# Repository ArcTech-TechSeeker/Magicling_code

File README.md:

# Magicling_code（nIpxel用コード）

モーション入力＆ハプティクス付き **無線コントローラ nIpxel**（ESP32 + BNO055）を中心としたコード/回路/CADである。
9 軸センサから得た姿勢・加速度を**世界座標へ変換**し、**Bluetooth SPP** でホストへ送出すると同時に、振動モータを **PWM** で制御する。

紹介サイト：https://nipxel.netlify.app/

---

## 特長

* **9軸姿勢融合**：BNO055（NDOF）から **Yaw / Pitch / Roll** と **線形加速度**を取得
* **座標安定化**：クォータニオン→回転行列で**グローバル座標系加速度**を算出
* **ジャンプ補償**：Yaw のスパイク（磁気外乱等）を短時間固定＋オフセットで自然連続化
* **ハプティクス**：振動モータを **200 Hz / 8bit PWM** で駆動（アナログ追従／点滅パターン）
* **軽量通信**：Bluetooth SPP で **固定小数バイナリ**（15 B/フレーム）を周期送信
* **2P対応**：デバイス名末尾を `"1P"` / `"2P"` で切替

---

## アーキテクチャ

```
BNO055 → (I²C) → ESP32 (LoLin32 Lite 等)
         ├─ クォータニオン姿勢 → 回転行列 → 世界座標加速度
         ├─ ジャンプ補償（Yaw offset）
         ├─ ハプティクス制御（PWM）
         └─ Bluetooth SPP（固定小数バイナリ）→ PC / ゲーム
```

---

## ハードウェア

* **MCU**：ESP32（LoLin32 Lite 等）
* **IMU**：Adafruit BNO055（I²C, アドレス `0x29`）
* **モータ**：小型振動モータ（ローサイド NPN 駆動：2SC1815）
* **ベース抵抗**：**1 kΩ（茶・黒・赤・金）**
* **フライバック**：1N400x 等（モータ端子**並列・逆向き**）

### 回路データ
回路データはCircuitフォルダ内のもの．Kicadを用いて作成されている．

PCBを発注したければ，GaberのZIPファイルを直接JLCPCBなどのサービスに発注するとよい

### CADデータ
AutodeskのInventorを用いて製作．プリントしたい場合はfor 3Dprintフォルダ内のSTLを使用

### 既定ピン

| 機能       | ESP32 ピン    | 備考                  |
| -------- | ----------- | ------------------- |
| I²C SDA  | GPIO **23** | `Wire.begin(23,19)` |
| I²C SCL  | GPIO **19** | 〃                   |
| PWM（モータ） | GPIO **25** | 200 Hz / 8bit       |
| LED      | GPIO **22** | 動作表示                |

> 3.3 V／GND 共有。I²C は 4.7–10 kΩ のプルアップ（多くのブレークアウトに実装済み）。

---

## ファームウェア概要

### 主要ライブラリ

`Wire.h`（I²C）、`Adafruit_BNO055.h`（9軸融合）、`utility/imumaths.h`（Quat/行列）、`BluetoothSerial.h`（SPP）

### PWM 互換層

ESP32 Arduino Core v2/v3 の差異をマクロで吸収（`ledcSetup/AttachPin` vs `ledcAttach`）。

### センサ処理パイプライン

1. **取得**：BNO055 から **線形加速度**・**オイラー角**・**クォータニオン**
2. **平滑化**：加速度[g]に一次 IIR（`alpha=0.7`）
3. **座標変換**：Quat→3×3 回転行列でローカル→**世界座標系**へ
4. **Yaw 補償**：差分 > 45°（かつ < 320°）を「ジャンプ」とみなし短時間固定、後段で `yaw_offset` を適用

### ハプティクス（`Vibration()`）

* **モード選択**：SPP で `'0'..'5'` の一文字コマンド

  * `'0'`：アナログ追従（|a| からデューティ算出、下限デッドゾーン・上限クランプ）
  * `'1'..'4'`：点滅パターン（周期×デューティ）
  * `'5'`：停止

---

## Bluetooth SPP プロトコル

**1 フレーム = 15 バイト**

* 先頭ヘッダ：`'S'`（1 B）
* ペイロード：**int16 × 7**（14 B, Little-Endian）

  1. `ax_global × 100`（2桁固定小数）
  2. `ay_global × 100`
  3. `az_global × 100`
  4. `qw × 10000`（4桁固定小数）
  5. `qx × 10000`
  6. `qy × 10000`
  7. `qz × 10000`

**送信周期**：およそ **100 Hz**（`delay(10)` 目安）
**デコード（受信側）**：LE の `int16` を実数に復元（加速度÷100、Quaternion÷10000）。ヘッダ `'S'` で同期。

---

## ビルド & 書き込み

### Arduino IDE

1. ボード：ESP32 ファミリ（LoLin32 Lite 等）
2. 依存ライブラリ導入（Adafruit BNO055 ほか）
3. スケッチを書き込み

### PlatformIO / ESP-IDF

* `ledc` / `Wire` / `BluetoothSerial` が利用可能な環境設定でビルド。

---

## 起動と使用

1. 電源投入／SPP ペアリング：デバイス名は `"LOLIN32_Lite_1P"`（`name` で `"2P"` に切替可）
2. ホストは SPP で **15B 固定フレーム**を連続受信
3. 必要に応じ `'0'..'5'` を送信して**ハプティクスモード**を切替

---

## 調整可能パラメータ

| 変数              |     既定 | 説明         |
| --------------- | -----: | ---------- |
| `alpha`         |    0.7 | ローパス（過去重み） |
| `pwmFreq`       | 200 Hz | モータ駆動周波数   |
| `pwmResolution` |  8 bit | デューティ分解能   |
| `j_wall`        |  2 ループ | Yaw 固定期間   |
| `name`          | `"1P"` | SPP 名末尾    |

---

## リポジトリ構成（例）

```
Magicling_code/
├── src/                # ESP32 スケッチ/ソース
├── include/            # ヘッダ
├── hardware/           # 回路図・配線図
└── README.md
```

> 実際の構成はリポジトリに従うこと。名称や配置は変更される場合がある。

## ライセンス

リポジトリ同梱の **LICENSE** を参照。
# Magicling_code (Code for nIpxel)

This repository contains the code, circuit data, and CAD resources centered around **nIpxel**, a **wireless controller with motion input and haptics** (ESP32 + BNO055).

It converts orientation/acceleration obtained from a 9-axis sensor into the **world (global) coordinate frame**, transmits the data to a host via **Bluetooth SPP**, and controls a vibration motor using **PWM**.

Project site: https://nipxel.netlify.app/

---

## Features

- **9-axis sensor fusion**: Uses BNO055 (NDOF) to obtain **Yaw / Pitch / Roll** and **linear acceleration**
- **Coordinate stabilization**: Converts quaternion → rotation matrix to compute **global-frame acceleration**
- **Jump compensation**: Detects yaw spikes (e.g., magnetic disturbance), briefly freezes + applies an offset for smooth continuity
- **Haptics**: Drives a vibration motor at **200 Hz / 8-bit PWM** (analog follow / blink patterns)
- **Lightweight transport**: Periodically sends **fixed-point binary** frames over Bluetooth SPP (**15 B/frame**)
- **Two-player support**: Switch the device name suffix to `"1P"` / `"2P"`

---

## Architecture

```text
BNO055 → (I²C) → ESP32 (LoLin32 Lite, etc.)
         ├─ Quaternion orientation → Rotation matrix → World-frame acceleration
         ├─ Jump compensation (yaw offset)
         ├─ Haptics control (PWM)
         └─ Bluetooth SPP (fixed-point binary) → PC / game
```

---

## Hardware

- **MCU**: ESP32 (LoLin32 Lite, etc.)
- **IMU**: Adafruit BNO055 (I²C, address `0x29`)
- **Motor**: Small vibration motor (low-side NPN drive: 2SC1815)
- **Base resistor**: **1 kΩ (brown-black-red-gold)**
- **Flyback diode**: 1N400x, etc. (in parallel across motor terminals, reverse polarity)

### Circuit Data

Circuit data is located in the `Circuit` folder and was created using **KiCad**.

If you want to order a PCB, you can upload the **Gerber ZIP** directly to services such as **JLCPCB**.

### CAD Data

Designed using **Autodesk Inventor**. For 3D printing, use the STL files in the `for 3Dprint` folder.

### Default Pins

| Function        | ESP32 Pin     | Notes               |
|----------------|---------------|---------------------|
| I²C SDA        | GPIO **23**   | `Wire.begin(23,19)` |
| I²C SCL        | GPIO **19**   | same as above       |
| PWM (motor)    | GPIO **25**   | 200 Hz / 8-bit      |
| LED            | GPIO **22**   | status indicator    |

> Share 3.3 V / GND. I²C requires 4.7–10 kΩ pull-ups (often included on breakout boards).

---

## Firmware Overview

### Key Libraries

`Wire.h` (I²C), `Adafruit_BNO055.h` (sensor fusion), `utility/imumaths.h` (Quat/matrix), `BluetoothSerial.h` (SPP)

### PWM Compatibility Layer

Absorbs differences between ESP32 Arduino Core v2/v3 using macros (e.g., `ledcSetup/AttachPin` vs `ledcAttach`).

### Sensor Processing Pipeline

1. **Read**: From BNO055: **linear acceleration**, **Euler angles**, **quaternion**
2. **Smoothing**: First-order IIR on acceleration [g] (`alpha=0.7`)
3. **Transform**: Quat → 3×3 rotation matrix; local → **world frame**
4. **Yaw compensation**: If delta > 45° (and < 320°), treat as a “jump”, freeze briefly; apply `yaw_offset` afterward

### Haptics (`Vibration()`)

- **Mode selection**: Send a single-character command via SPP: `'0'..'5'`

  - `'0'`: Analog follow (compute duty from |a| with deadzone and clamp)
  - `'1'..'4'`: Blink patterns (period × duty)
  - `'5'`: Stop

---

## Bluetooth SPP Protocol

**1 frame = 15 bytes**

- Header: `'S'` (1 B)
- Payload: **int16 × 7** (14 B, Little-Endian)

  1. `ax_global × 100` (fixed-point with 2 decimals)
  2. `ay_global × 100`
  3. `az_global × 100`
  4. `qw × 10000` (fixed-point with 4 decimals)
  5. `qx × 10000`
  6. `qy × 10000`
  7. `qz × 10000`

**Transmit rate**: approx. **100 Hz** (target via `delay(10)`)  
**Decode (receiver)**: Convert LE `int16` back to float (accel ÷ 100, quaternion ÷ 10000). Use header `'S'` for synchronization.

---

## Build & Flash

### Arduino IDE

1. Board: ESP32 family (LoLin32 Lite, etc.)
2. Install dependencies (Adafruit BNO055, etc.)
3. Upload the sketch

### PlatformIO / ESP-IDF

- Build with an environment where `ledc`, `Wire`, and `BluetoothSerial` are available.

---

## Startup & Usage

1. Power on / pair via SPP: device name defaults to `"LOLIN32_Lite_1P"` (set `name` to switch to `"2P"`)
2. Host continuously receives **15-byte fixed frames** over SPP
3. Send `'0'..'5'` as needed to switch **haptics modes**

---

## Tunable Parameters

| Variable          | Default  | Description            |
|------------------|---------:|------------------------|
| `alpha`          |    0.7   | Low-pass filter weight |
| `pwmFreq`        | 200 Hz   | Motor drive frequency  |
| `pwmResolution`  |  8 bit   | PWM duty resolution    |
| `j_wall`         | 2 loops  | Yaw freeze duration    |
| `name`           | `"1P"`   | SPP name suffix        |

---

## Repository Layout (Example)

```text
Magicling_code/
├── src/                # ESP32 sketch/source
├── include/            # headers
├── hardware/           # schematics/wiring
└── README.md
```

> Follow the actual repository structure. Names and locations may change.

---

## License

See the **LICENSE** file included in this repository.

---

## BLE OTA

The firmware exposes the same BLE OTA protocol as
`naka6ryo/RemoteCompilerToMicon` WebAppSide, without adding Wi-Fi
provisioning.

* BLE device name during the first 10 seconds after boot:
  `ESP32-nIpxel_1P` or `ESP32-nIpxel_2P`
* OTA service: `9f5f0001-8d9e-6f4e-bd0c-3c4d5e6f7180`
* Control: `START:<size>`, `END`, `ABORT`
* Data: binary firmware chunks
* Status: `READY`, `PROGRESS:x/y`, `SUCCESS`, `ERROR:*`

Use an ESP32 partition scheme with OTA slots. The VS Code/Arduino CLI settings
use `PartitionScheme=min_spiffs`, which gives the OTA app slot 1,966,080 bytes.
The PlatformIO settings use `partitions_ota_2m.csv`, matching the referenced
BLE OTA project.

## Game BLE Service

The device also exposes the game-facing BLE service used by
`BleControllerAdapter.js`.

* BLE device name after the OTA pairing window: `nIpxel_1P` or `nIpxel_2P`
* Service: `12345678-1234-1234-1234-123456789abc`
* Sensor Notify: `12345678-1234-1234-1234-123456789abd`
* Haptic Write: `12345678-1234-1234-1234-123456789abe`
* Sensor frame: 17 bytes, `S` + sequence byte + seven little-endian `int16` values + flags byte
* Haptic command: 2 bytes, `strength` and `duration` in 10 ms units

Arduino CLI build outputs are written to the workspace-local `build/` folder.

BLE advertising is mode-switched to keep Web Bluetooth filters reliable:
the first 10 seconds after boot advertise only the OTA service, and then the
device advertises only the game service. If an OTA client connects during that
initial window, OTA mode is kept active while connected.

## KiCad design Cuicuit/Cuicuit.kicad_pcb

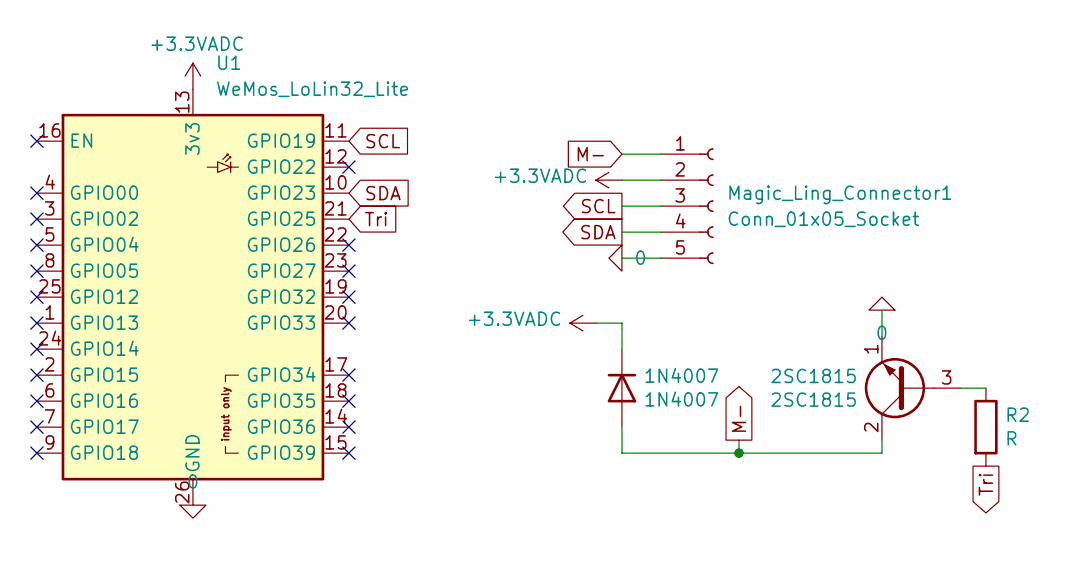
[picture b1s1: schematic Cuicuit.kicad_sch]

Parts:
1N4007: 1N4007; R_Axial_DIN0207_L6.3mm_D2.5mm_P10.16mm_Horizontal
2SC1815: 2SC1815; TO-92_Inline_Wide
Magic_Ling_Connector1: Conn_01x05_Socket; JST_PH_B5B-PH-K_1x05_P2.00mm_Vertical
R2: R; R_Axial_DIN0207_L6.3mm_D2.5mm_P10.16mm_Horizontal
U1: WeMos_LoLin32_Lite; WEMOS_LoLin32_Lite

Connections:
0: 2SC1815.1 (E), Magic_Ling_Connector1.5, U1.26 (GND)
+3.3VADC: 1N4007.1 (K), Magic_Ling_Connector1.2, U1.13 (3v3)
M-: 1N4007.2 (A), 2SC1815.2 (C), Magic_Ling_Connector1.1
unnamed: 2SC1815.3 (B), R2.1
SCL: Magic_Ling_Connector1.3, U1.11 (GPIO19)
SDA: Magic_Ling_Connector1.4, U1.10 (GPIO23)
Tri: R2.2, U1.21 (GPIO25)

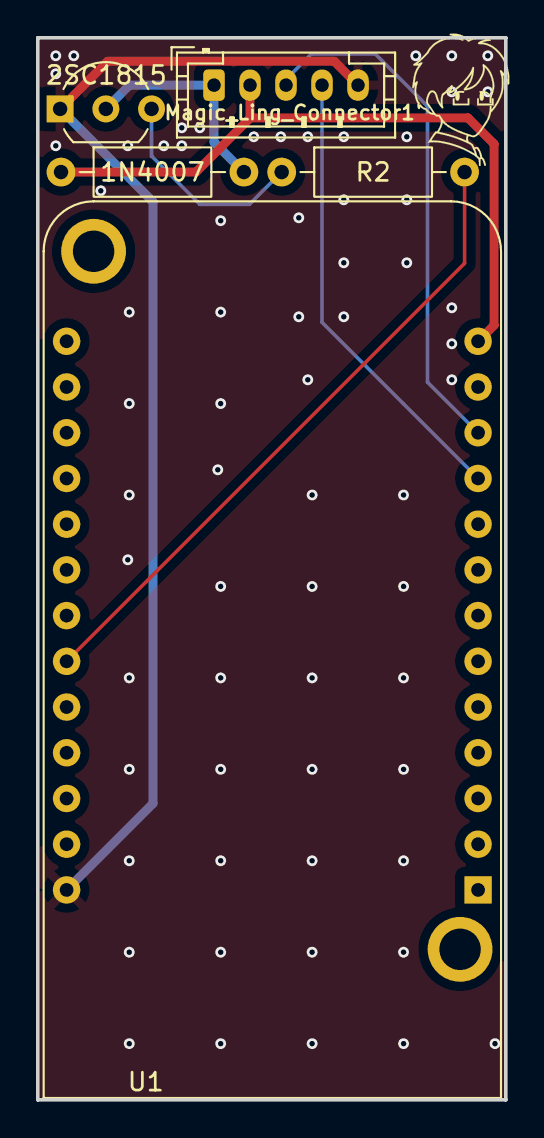
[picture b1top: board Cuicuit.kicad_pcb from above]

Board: 2 copper layers, 26.0 x 59.0 mm, 5 parts (0 on the bottom side), 7 nets.

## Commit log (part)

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2025-07-31 VScode上での書き込みの実装
2025-07-31 攻撃判定時に画面を白く光らす
2025-08-01 attack時の向いている向きの取得の試み（Yawのオイラーの値の飛びを判定して補正する）
2025-08-01 Yaw角の値の飛びの修正
2025-08-01 コードを関数を用いて整理，コメントの追加
2025-08-01 attack_yawの文字の色の変更
2025-08-02 振動モータ機能の追加（加速度により強さが変化）
2025-08-06 Bluetooth通信と詠唱状態（Spell：指を立てる，Spell2：動かし続ける）の追加
2025-08-06 名前変更
2025-08-08 ちょい変
2025-08-21 Lolin用の更新およびライブラシの整理
2025-08-21 ライブラリ対応
2025-08-22 判定の微調整
2025-09-24 加速度と３軸角度の通信
2025-09-27 受信の改良
2025-10-06 方向修正プログラムの実装
2025-10-07 ピッチとロール角の取得方法変更でのヨー角の精度向上（ピッチ・ロールはまだ変・・・今回はいいけど今後直していきたい）
2025-10-21 Add README with game overview and technical details
    Added detailed game overview, features, architecture, hardware specifications, firmware summary, and usage instructions for the '詠印魔道' game and associated code.
2026-01-13 Add CAD data and Circuit data
2026-01-13 Update README with project introduction and data details
    Added introduction and details about circuit and CAD data.
2026-01-17 Update Arduino configuration and enhance BLE functionality in the Magicling code
2026-01-17 Enhance BLE connection handling and improve data notification stability
2026-01-17 Add acceleration-based haptic feedback functionality and improve feedback handling
2026-01-30 Enhance README with project details and instructions
    Added detailed project description, features, architecture, hardware specifications, firmware overview, Bluetooth SPP protocol, build instructions, startup usage, tunable parameters, and repository l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
2026-05-22 Add initial project files and configuration for OTA updates
    - Created ELF, MAP, and partition binary files for the Magicling project.
    - Added partition configuration in `partitions_ota_2m.csv` for OTA updates.
    - Set up PlatformIO configuration in `platformio.ini` for the lolin32_lite board.
    - Defined source and library directories for the project structure.
2026-05-23 Add ArduinoJson and Madgwick libraries
    - Added ArduinoJson version header file to define the library version.
    - Introduced Madgwick library with implementation of the MadgwickAHRS algorithm for orientation estimation using accelerometer and gyroscope data.
    - Included README documentation for the Madgwick library detailing its usage and licensing.
    - Implemented core functionality in MadgwickAHRS.cpp and declared necessary functions in MadgwickAHRS.h.
2026-05-23 Remove Madgwick library files and add flatten build script
    - Deleted the Madgwick library files including README, source implementation, and header files.
    - Added a new script `flatten_build.py` to streamline the build process by copying the firmware binary to a flat build directory.
    - Updated `platformio.ini` to include the new script in the build process.
